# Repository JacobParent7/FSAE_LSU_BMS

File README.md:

# Motherboard

# Goal

Develop a distributed Battery Management System (BMS) for LSU FSAE's electric accumulator to be used in 2026 competition, targeting completion by May, 2025. All hardware and firmware development will be documented in this repository.

# Contact Info
### Motherboard Design
- Jacob Parent - jparen6@lsu.edu
### Daughterboard Design
- Parth Mistry - pmistr2@lsu.edu
- Modhy Alsahood - malsah1@lsu.edu

# FSAE BMS Design Log

## System Level Description 

## Orion BMS Thermistor Expansion Reverse Engineering

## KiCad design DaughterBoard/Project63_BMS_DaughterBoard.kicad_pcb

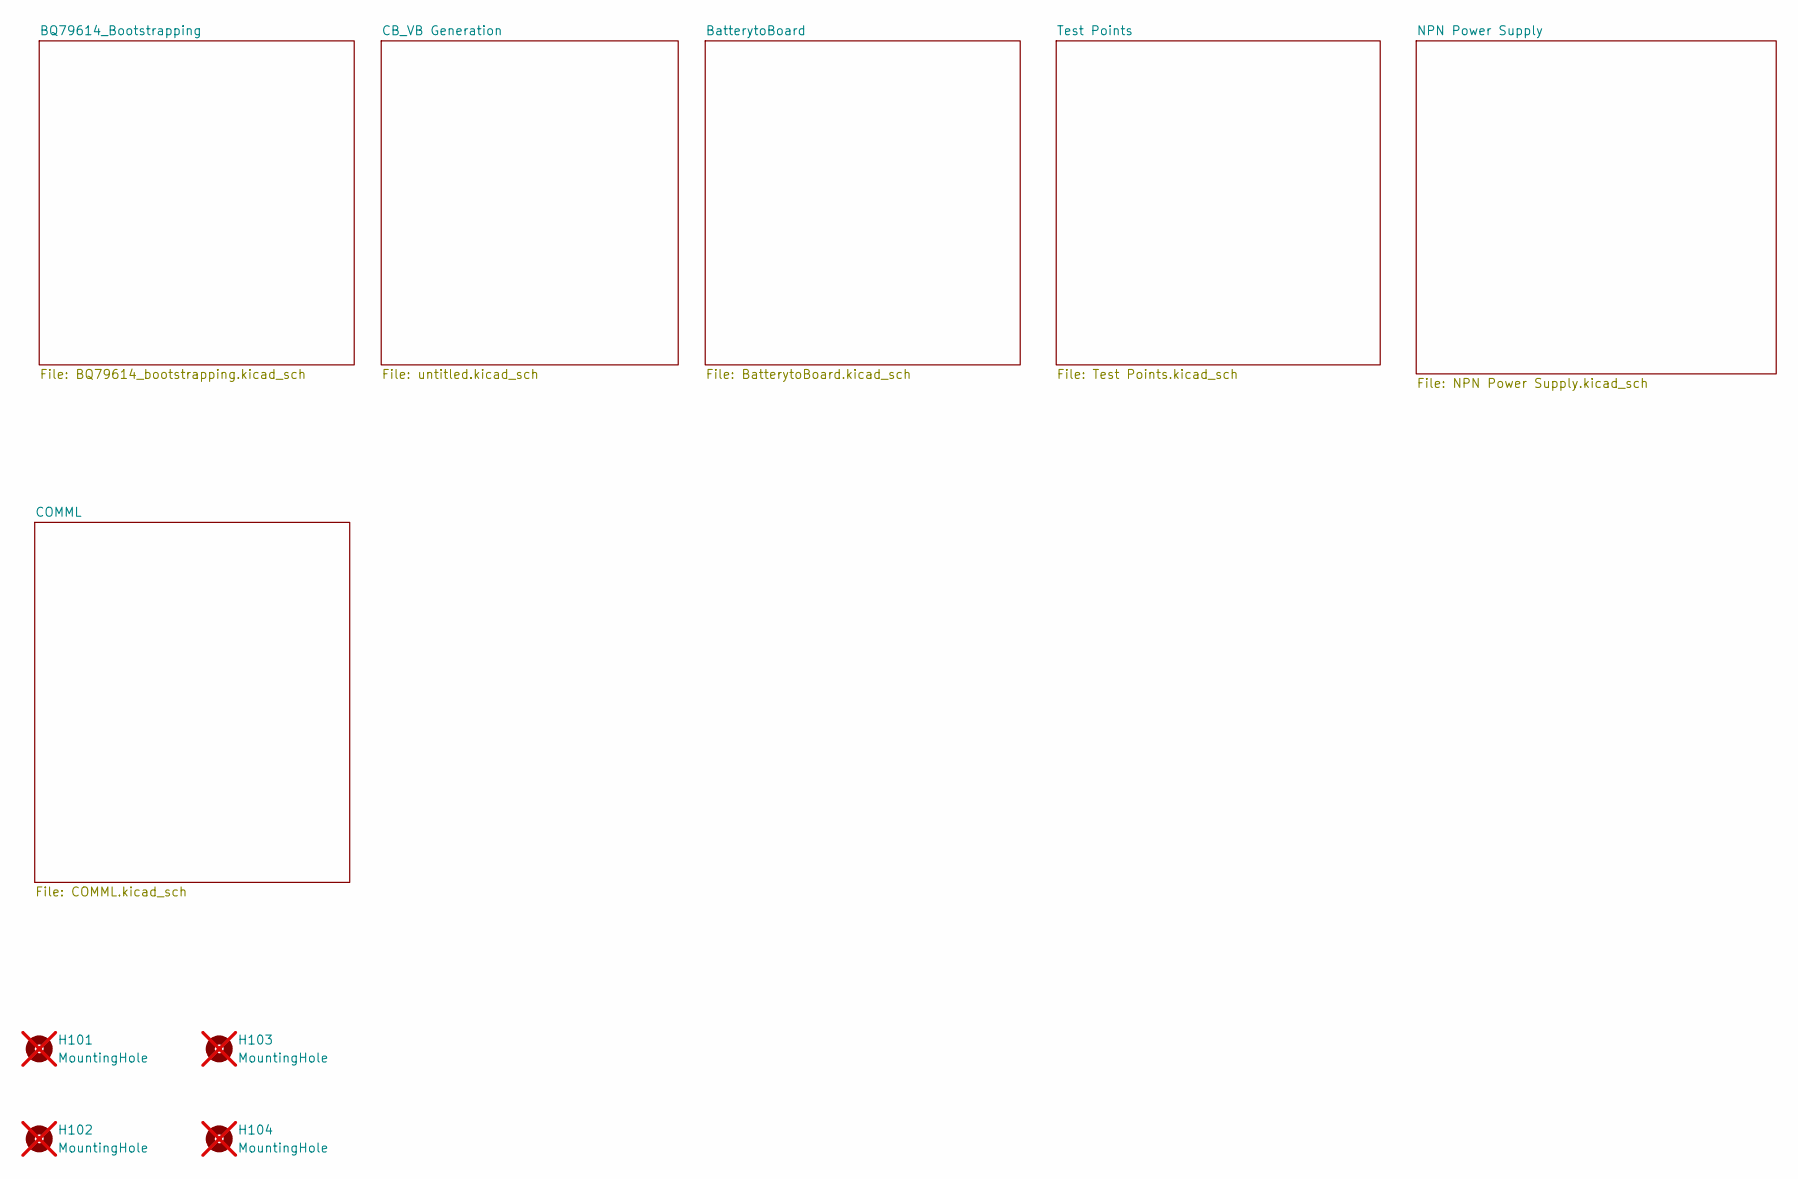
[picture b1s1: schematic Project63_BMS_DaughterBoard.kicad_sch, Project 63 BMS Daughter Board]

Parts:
H101, H102, H103, H104: MountingHole; MountingHole_3.2mm_M3; not fitted

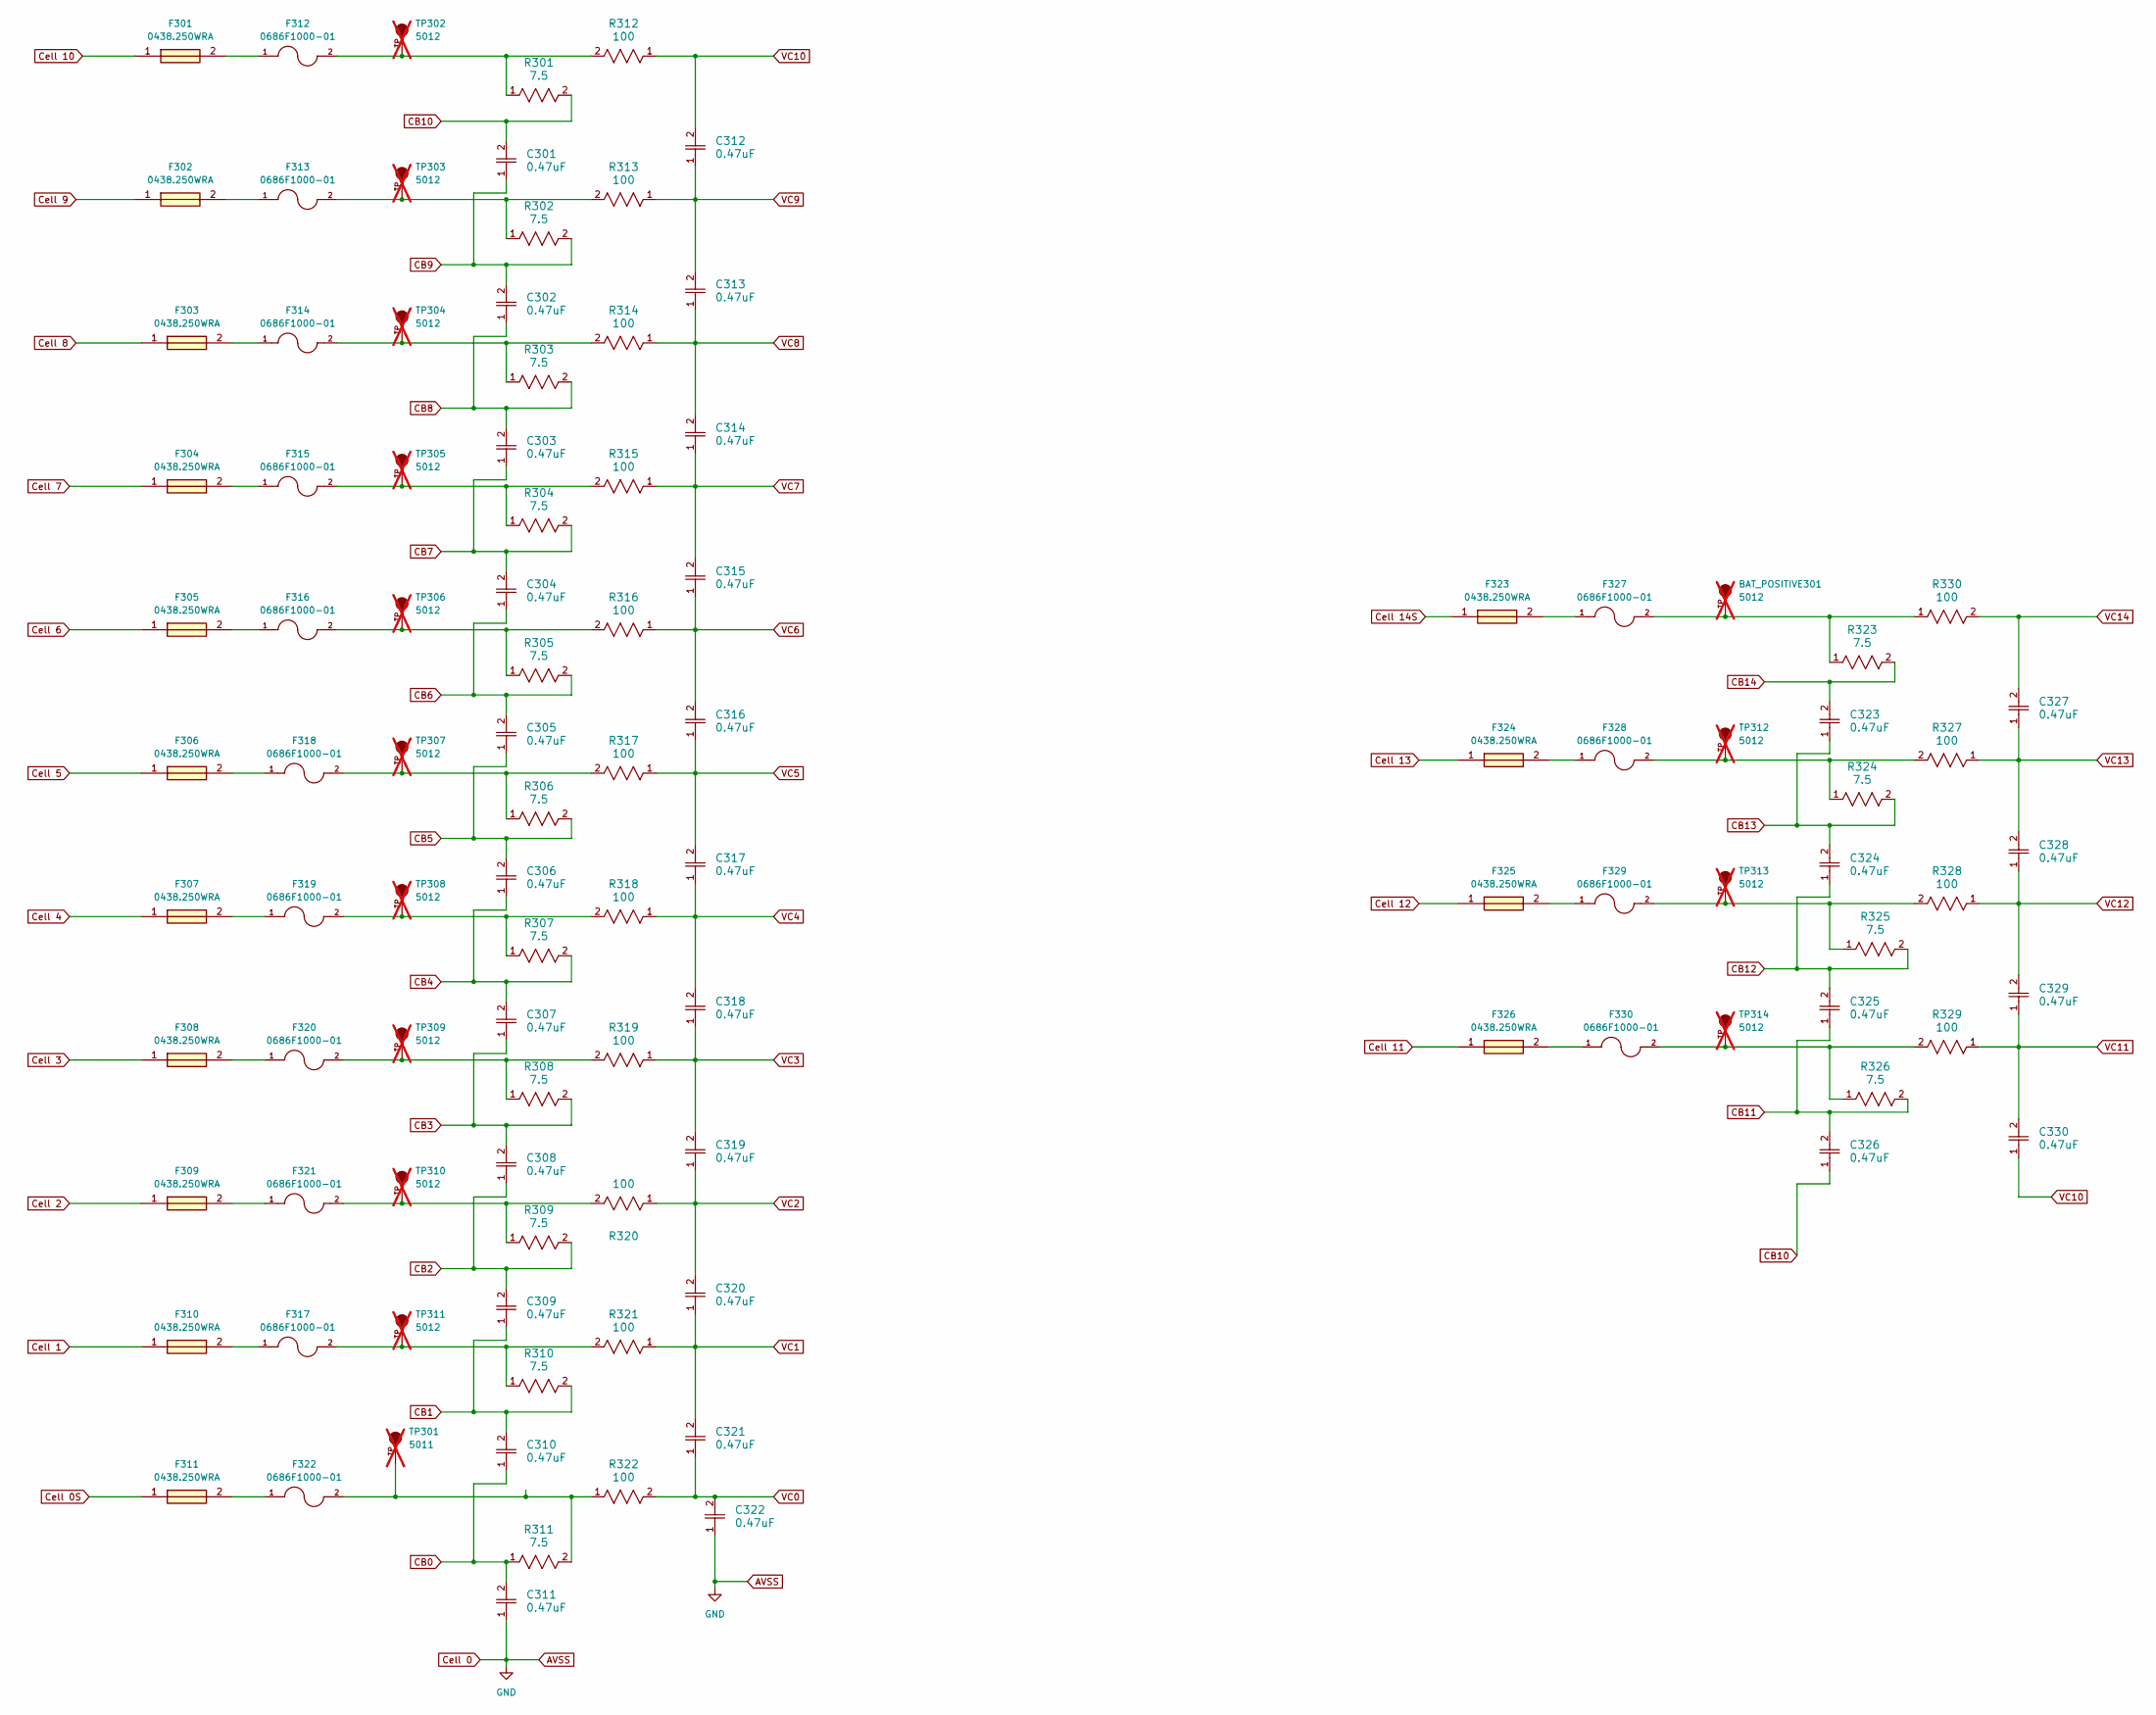
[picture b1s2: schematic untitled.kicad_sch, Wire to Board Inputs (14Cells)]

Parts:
BAT_POSITIVE301: 5012; TP_5012; PARTREV F; not fitted
C301, C302, C303, C304, C305, C306, C307, C308, C309, C310, C311, C312, C313, C314, C315, C316, C317, C318, C319, C320, C321, C322, C323, C324, C325, C326, C327, C328, C329, C330: 0.47uF; G-188_MUR-L; Manufacturer Part Number GCM188R71C474KA55D; JLC PCB Part # C161214
F301, F302, F303, F304, F305, F306, F307, F308, F309, F310, F311, F323, F324, F325, F326: 0438.250WRA; Fuse_0603_1608Metric; Manufacturer_Part_Number 0438.250WRA; Mouser Part Number 576-0438.250WRA
F312, F313, F314, F315, F316, F317, F318, F319, F320, F321, F322, F327, F328, F329, F330: 0686F1000-01; FUSC1608X60N; PARTREV Jan2019; JLC PCB Part # C136329
R301, R302, R303, R304, R305, R306, R307, R308, R309, R310, R311, R323, R324, R325, R326: 7.5; R_1812_4532Metric; Manufacturer Part Number FRC1812J7R5 TS; JLC PCB Part # C5204035
R312, R313, R314, R315, R316, R317, R318, R319, R320, R321, R322, R327, R328, R329, R330: 100; R_0603_1608Metric; Manufacturer Part Number HoAR0603-1/10W-100R-0.1%-TCR25; JLC PCB Part # C5123580
TP301: 5011; TP_5011; PARTREV F; not fitted
TP302, TP303, TP304, TP305, TP306, TP307, TP308, TP309, TP310, TP311, TP312, TP313, TP314: 5012; TP_5012; PARTREV F; not fitted

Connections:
AVSS: C311.1, C322.1; also elsewhere on the board
CB0: C310.1, C311.2, R311.1; also elsewhere on the board
CB1: C309.1, C310.2, R310.2; also elsewhere on the board
CB2: C308.1, C309.2, R309.2; also elsewhere on the board
CB3: C307.1, C308.2, R308.2; also elsewhere on the board
CB4: C306.1, C307.2, R307.2; also elsewhere on the board
CB5: C305.1, C306.2, R306.2; also elsewhere on the board
CB6: C304.1, C305.2, R305.2; also elsewhere on the board
CB7: C303.1, C304.2, R304.2; also elsewhere on the board
CB8: C302.1, C303.2, R303.2; also elsewhere on the board
CB9: C301.1, C302.2, R302.2; also elsewhere on the board
CB10: C301.2, C326.1, R301.2; also elsewhere on the board
CB11: C325.1, C326.2, R326.2; also elsewhere on the board
CB12: C324.1, C325.2, R325.2; also elsewhere on the board
CB13: C323.1, C324.2, R324.2; also elsewhere on the board
CB14: C323.2, R323.2; also elsewhere on the board
Cell 0S: F311.1; also elsewhere on the board
Cell 1: F310.1; also elsewhere on the board
Cell 2: F309.1; also elsewhere on the board
Cell 3: F308.1; also elsewhere on the board
Cell 4: F307.1; also elsewhere on the board
Cell 5: F306.1; also elsewhere on the board
Cell 6: F305.1; also elsewhere on the board
Cell 7: F304.1; also elsewhere on the board
Cell 8: F303.1; also elsewhere on the board
Cell 9: F302.1; also elsewhere on the board
Cell 10: F301.1; also elsewhere on the board
Cell 11: F326.1; also elsewhere on the board
Cell 12: F325.1; also elsewhere on the board
Cell 13: F324.1; also elsewhere on the board
Cell 14S: F323.1; also elsewhere on the board
unnamed: BAT_POSITIVE301.TP, F327.2, R323.1, R330.1
unnamed: F301.2, F312.1
unnamed: F302.2, F313.1
unnamed: F303.2, F314.1
unnamed: F304.2, F315.1
unnamed: F305.2, F316.1
unnamed: F306.2, F318.1
unnamed: F307.2, F319.1
unnamed: F308.2, F320.1
unnamed: F309.2, F321.1
unnamed: F310.2, F317.1
unnamed: F311.2, F322.1
unnamed: F312.2, R301.1, R312.2, TP302.TP
unnamed: F313.2, R302.1, R313.2, TP303.TP
unnamed: F314.2, R303.1, R314.2, TP304.TP
unnamed: F315.2, R304.1, R315.2, TP305.TP
unnamed: F316.2, R305.1, R316.2, TP306.TP
unnamed: F317.2, R310.1, R321.2, TP311.TP
unnamed: F318.2, R306.1, R317.2, TP307.TP
unnamed: F319.2, R307.1, R318.2, TP308.TP
unnamed: F320.2, R308.1, R319.2, TP309.TP
unnamed: F321.2, R309.1, R320.2, TP310.TP
unnamed: F322.2, R311.2, R322.1, TP301.TP
unnamed: F323.2, F327.1
unnamed: F324.2, F328.1
unnamed: F325.2, F329.1
unnamed: F326.2, F330.1
unnamed: F328.2, R324.1, R327.2, TP312.TP
unnamed: F329.2, R325.1, R328.2, TP313.TP
unnamed: F330.2, R326.1, R329.2, TP314.TP
VC0: C321.1, C322.2, R322.2; also elsewhere on the board
VC1: C320.1, C321.2, R321.1; also elsewhere on the board
VC2: C319.1, C320.2, R320.1; also elsewhere on the board
VC3: C318.1, C319.2, R319.1; also elsewhere on the board
VC4: C317.1, C318.2, R318.1; also elsewhere on the board
VC5: C316.1, C317.2, R317.1; also elsewhere on the board
VC6: C315.1, C316.2, R316.1; also elsewhere on the board
VC7: C314.1, C315.2, R315.1; also elsewhere on the board
VC8: C313.1, C314.2, R314.1; also elsewhere on the board
VC9: C312.1, C313.2, R313.1; also elsewhere on the board
VC10: C312.2, C330.1, R312.1; also elsewhere on the board
VC11: C329.1, C330.2, R329.1; also elsewhere on the board
VC12: C328.1, C329.2, R328.1; also elsewhere on the board
VC13: C327.1, C328.2, R327.1; also elsewhere on the board
VC14: C327.2, R330.2; also elsewhere on the board

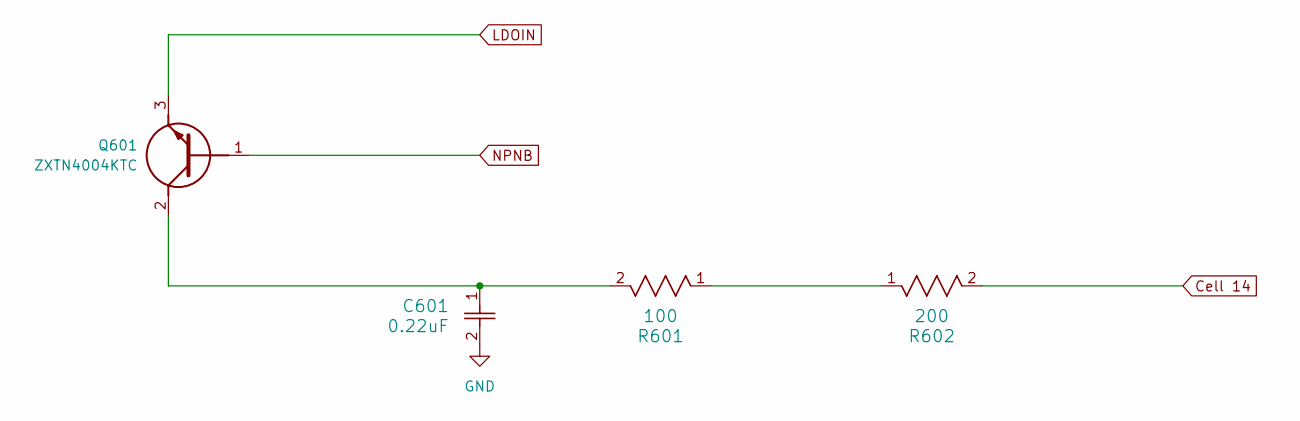
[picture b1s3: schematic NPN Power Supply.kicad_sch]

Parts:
C601: 0.22uF; G-31_MUR-L; Manufacturer Part Number GCM31MR72A224KA37L; JLC PCB Part # C161277
Q601: ZXTN4004KTC; Mouser Part Number 621-ZXTN4004KTC
R601: 100; RES_CRCW_2010-L; Manufacturer Part Number WF20P1000FTL; JLC PCB Part # C305269
R602: 200; R_2512_6332Metric; Manufacturer Part Number RC2512JK-07200RL; JLC PCB Part # C2935248

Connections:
AVSS: C601.2; also elsewhere on the board
BAT: R602.2; also elsewhere on the board
LDOIN: Q601.3 (E); also elsewhere on the board
NPNB: Q601.1 (B); also elsewhere on the board
unnamed: C601.1, Q601.2 (C), R601.2
unnamed: R601.1, R602.1

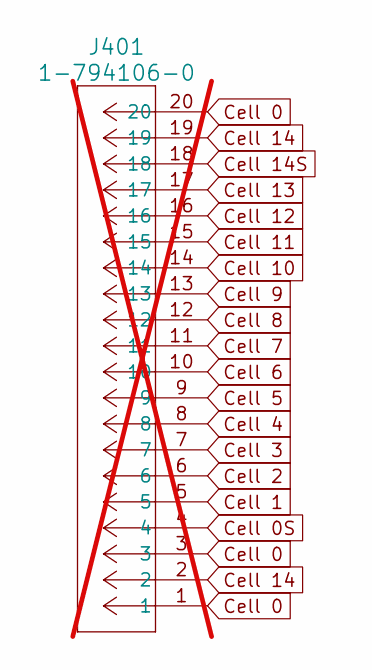
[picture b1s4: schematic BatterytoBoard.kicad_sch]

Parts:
J401: 1-794106-0; CON20_2X10_P4.14MM_RAMNL_TYC; not fitted

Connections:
AVSS: J401.1, J401.3, J401.20; also elsewhere on the board
BAT: J401.2, J401.19; also elsewhere on the board
Cell 0S: J401.4; also elsewhere on the board
Cell 1: J401.5; also elsewhere on the board
Cell 2: J401.6; also elsewhere on the board
Cell 3: J401.7; also elsewhere on the board
Cell 4: J401.8; also elsewhere on the board
Cell 5: J401.9; also elsewhere on the board
Cell 6: J401.10; also elsewhere on the board
Cell 7: J401.11; also elsewhere on the board
Cell 8: J401.12; also elsewhere on the board
Cell 9: J401.13; also elsewhere on the board
Cell 10: J401.14; also elsewhere on the board
Cell 11: J401.15; also elsewhere on the board
Cell 12: J401.16; also elsewhere on the board
Cell 13: J401.17; also elsewhere on the board
Cell 14S: J401.18; also elsewhere on the board

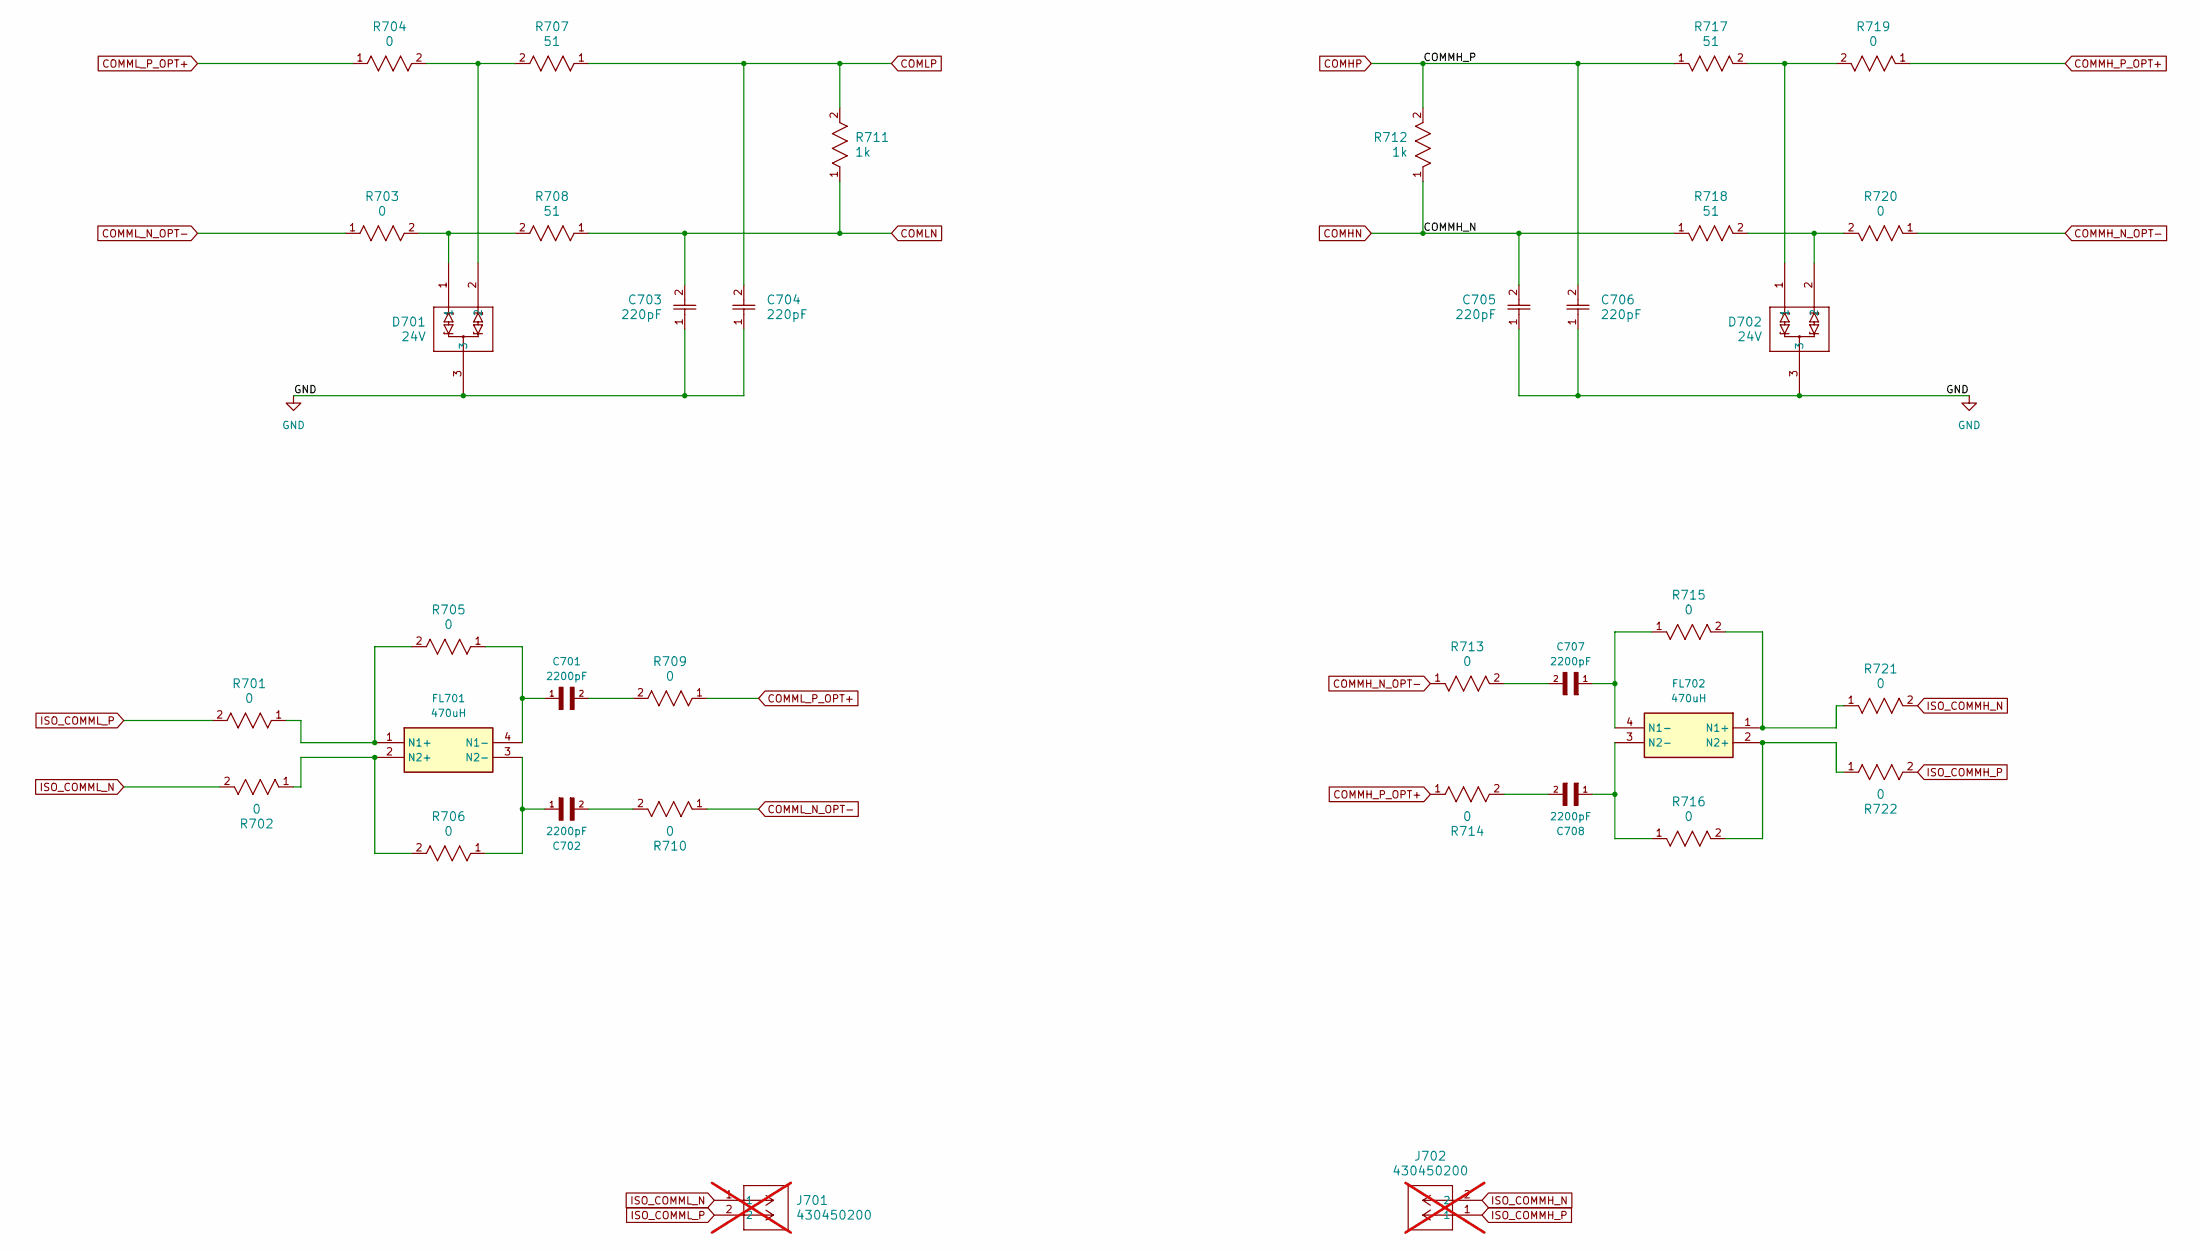
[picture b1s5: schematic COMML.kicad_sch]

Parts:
C701, C702, C707, C708: 2200pF; CAPC3216X160N; Manufacturer Part Number CC1206KKX7RCBB222; JLC PCB Part # C107194
C703, C704, C705, C706: 220pF; CAP_CL10_SAM-L; Manufacturer Part Number CC0603KRX7R9BB221; JLC PCB Part # C107081
D701, D702: 24V; SOT-23; Manufacturer Part Number PESD24VL2BTN; JLC PCB Part # C314266
FL701, FL702: 470uH; 744242471; Mouser Part Number 710-744242471
J701, J702: 430450200; CON_430450200_MOL; not fitted
R701, R702, R705, R706, R709, R710, R713, R714, R715, R716, R721, R722: 0; RES_CRCW_0805_VIS-L; Manufacturer Part Number CRCW08050000Z0EAHP; JLC PCB Part # C844811
R703, R704, R719, R720: 0; RC0603N_YAG-L; Manufacturer Part Number RC0603JR-070RL; JLC PCB Part # C95177
R707, R708, R717, R718: 51; RC0603N_VIS-L; Manufacturer Part Number CRCW060351R0JNEA; JLC PCB Part # C844178
R711, R712: 1k; RC0603N_PAN-L; Manufacturer Part Number FRC0603F1001TS; JLC PCB Part # C2907002

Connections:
AVSS: C703.1, C704.1, C705.1, C706.1, D701.3, D702.3; also elsewhere on the board
COMHN: C705.2, R712.1, R718.1; also elsewhere on the board
COMHP: C706.2, R712.2, R717.1; also elsewhere on the board
COMLN: C703.2, R708.1, R711.1; also elsewhere on the board
COMLP: C704.2, R707.1, R711.2; also elsewhere on the board
COMMH_N_OPT-: R713.1, R720.1
COMMH_P_OPT+: R714.1, R719.1
COMML_N_OPT-: R703.1, R710.1
COMML_P_OPT+: R704.1, R709.1
ISO_COMMH_N: J702.2, R721.2
ISO_COMMH_P: J702.1, R722.2
ISO_COMML_N: J701.1, R702.2
ISO_COMML_P: J701.2, R701.2
unnamed: C701.2, R709.2
unnamed: C702.2, R710.2
unnamed: C707.2, R713.2
unnamed: C708.2, R714.2
unnamed: D701.1, R703.2, R708.2
unnamed: D701.2, R704.2, R707.2
unnamed: D702.1, R717.2, R719.2
unnamed: D702.2, R718.2, R720.2
unnamed: FL701.1 (N1+), R701.1, R705.2
unnamed: C701.1, FL701.4 (N1-), R705.1
unnamed: FL701.2 (N2+), R702.1, R706.2
unnamed: C702.1, FL701.3 (N2-), R706.1
unnamed: FL702.1 (N1+), R715.2, R721.1
unnamed: C707.1, FL702.4 (N1-), R715.1
unnamed: FL702.2 (N2+), R716.2, R722.1
unnamed: C708.1, FL702.3 (N2-), R716.1

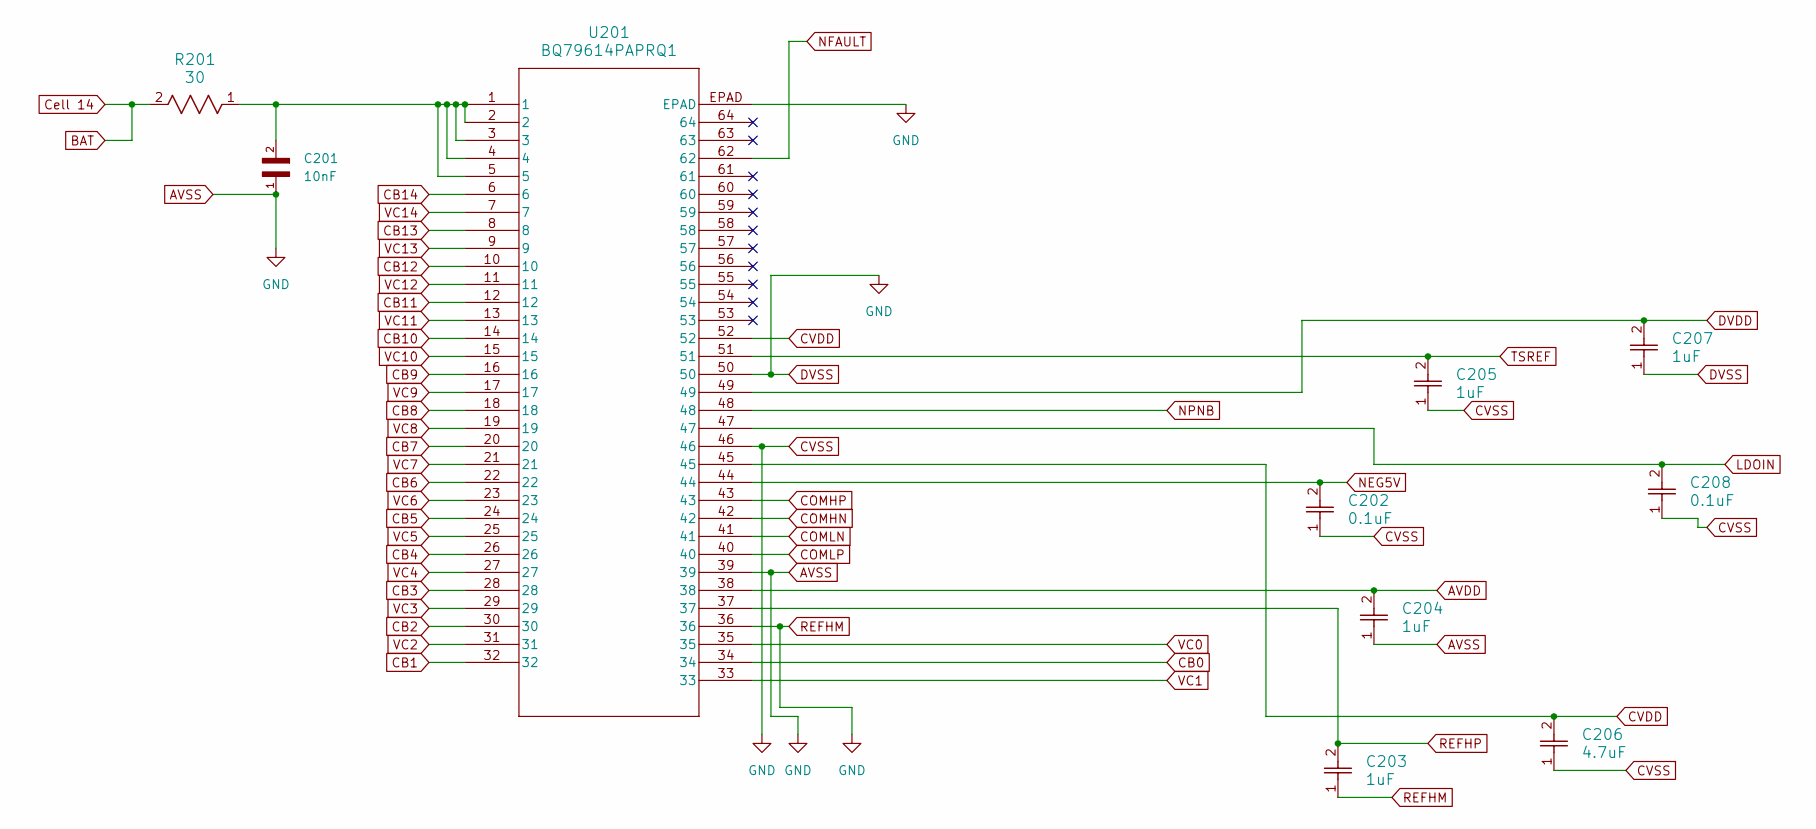
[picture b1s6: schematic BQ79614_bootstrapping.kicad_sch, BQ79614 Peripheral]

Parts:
C201: 10nF; CAPC1608X90N; Manufacturer Part Number GCM188R72A103KA37J; JLC PCB Part # C2167085
C202, C208: 0.1uF; CAP_GCM15_1p05X0p55X0p55_MUR-L; Manufacturer Part Number GCM155R71A104KA55D; JLC PCB Part # C161163
C203, C204, C205, C207: 1uF; CAPC18095_95N_KEM-L; Manufacturer Part Number CL10B105KA8NNNC; JLC PCB Part # C29936
C206: 4.7uF; CAP_2012_TDK-L; Manufacturer Part Number CC0805KKX7R7BB475; JLC PCB Part # C277499
R201: 30; RC0603N_PAN-L; Manufacturer Part Number ERJ-3EKF30R0V; JLC PCB Part # C403150
U201: BQ79614PAPRQ1; QFP_4PAPRQ1_TEX-L; Manufacturer Part Number BQ79616PAPRQ1; JLC PCB Part # C3682338

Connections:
AVDD: C204.2, U201.38; also elsewhere on the board
AVSS: C201.1, C202.1, C203.1, C204.1, C205.1, C206.1, C207.1, C208.1, U201.36, U201.39, U201.46, U201.50, U201.EPAD; also elsewhere on the board
BAT: R201.2; also elsewhere on the board
CB0: U201.34; also elsewhere on the board
CB1: U201.32; also elsewhere on the board
CB2: U201.30; also elsewhere on the board
CB3: U201.28; also elsewhere on the board
CB4: U201.26; also elsewhere on the board
CB5: U201.24; also elsewhere on the board
CB6: U201.22; also elsewhere on the board
CB7: U201.20; also elsewhere on the board
CB8: U201.18; also elsewhere on the board
CB9: U201.16; also elsewhere on the board
CB10: U201.14; also elsewhere on the board
CB11: U201.12; also elsewhere on the board
CB12: U201.10; also elsewhere on the board
CB13: U201.8; also elsewhere on the board
CB14: U201.6; also elsewhere on the board
COMHN: U201.42; also elsewhere on the board
COMHP: U201.43; also elsewhere on the board
COMLN: U201.41; also elsewhere on the board
COMLP: U201.40; also elsewhere on the board
CVDD: C206.2, U201.45, U201.52; also elsewhere on the board
DVDD: C207.2, U201.49; also elsewhere on the board
LDOIN: C208.2, U201.47; also elsewhere on the board
NEG5V: C202.2, U201.44; also elsewhere on the board
NFAULT: U201.62; also elsewhere on the board
NPNB: U201.48; also elsewhere on the board
unnamed: C201.2, R201.1, U201.1, U201.2, U201.3, U201.4, U201.5
REFHP: C203.2, U201.37; also elsewhere on the board
TSREF: C205.2, U201.51; also elsewhere on the board
VC0: U201.35; also elsewhere on the board
VC1: U201.33; also elsewhere on the board
VC2: U201.31; also elsewhere on the board
VC3: U201.29; also elsewhere on the board
VC4: U201.27; also elsewhere on the board
VC5: U201.25; also elsewhere on the board
VC6: U201.23; also elsewhere on the board
VC7: U201.21; also elsewhere on the board
VC8: U201.19; also elsewhere on the board
VC9: U201.17; also elsewhere on the board
VC10: U201.15; also elsewhere on the board
VC11: U201.13; also elsewhere on the board
VC12: U201.11; also elsewhere on the board
VC13: U201.9; also elsewhere on the board
VC14: U201.7; also elsewhere on the board

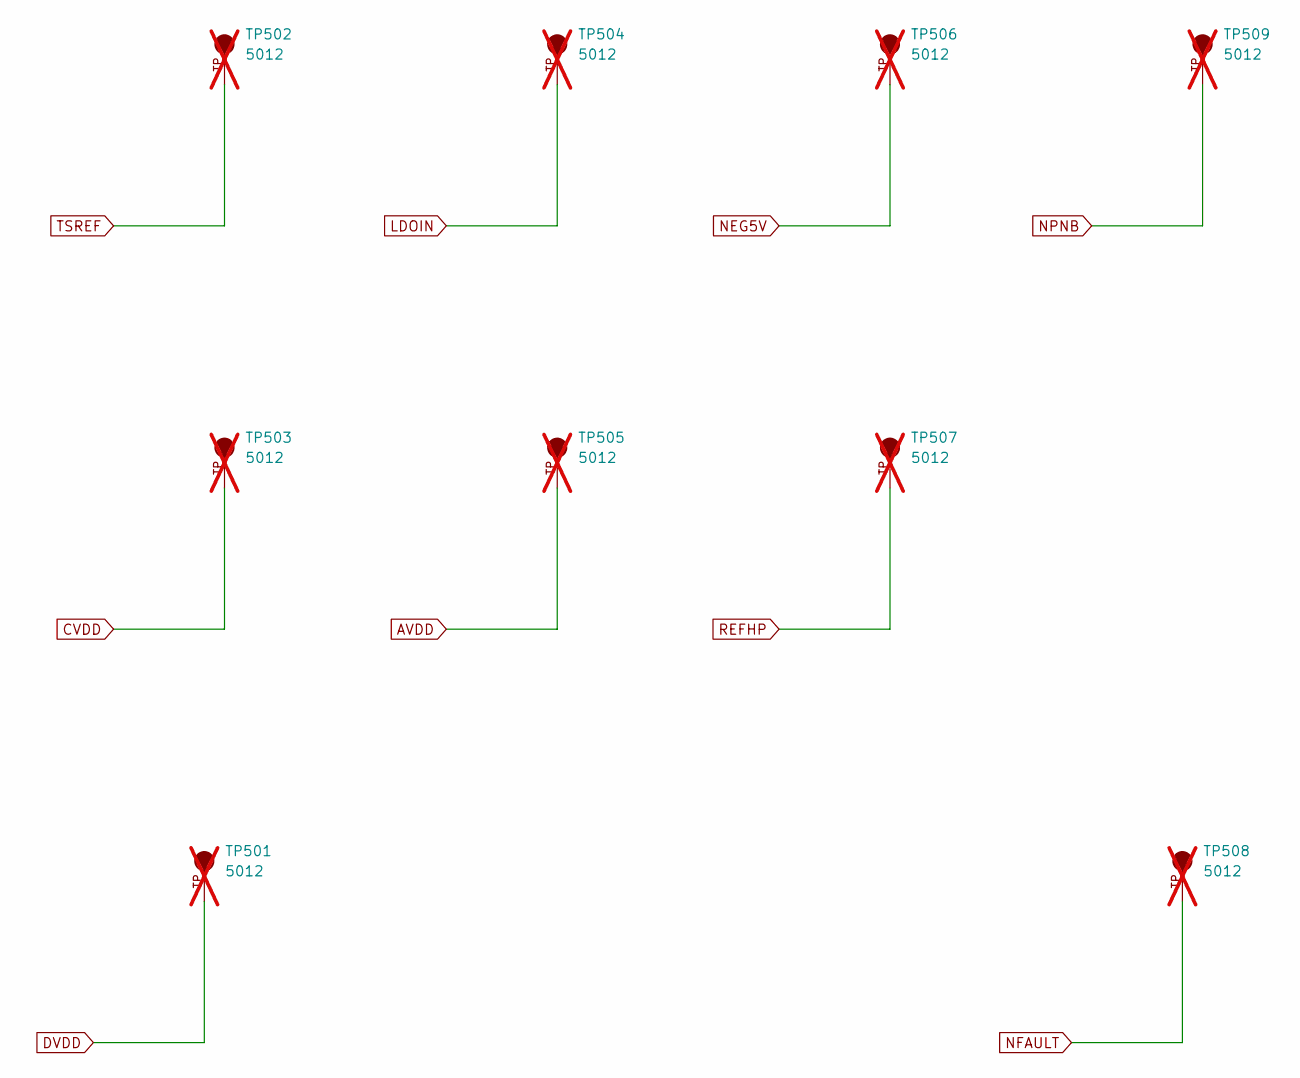
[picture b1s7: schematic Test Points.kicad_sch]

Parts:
TP501, TP502, TP503, TP504, TP505, TP506, TP507, TP508, TP509: 5012; TP_5012; PARTREV F; not fitted

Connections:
AVDD: TP505.TP; also elsewhere on the board
CVDD: TP503.TP; also elsewhere on the board
DVDD: TP501.TP; also elsewhere on the board
LDOIN: TP504.TP; also elsewhere on the board
NEG5V: TP506.TP; also elsewhere on the board
NFAULT: TP508.TP; also elsewhere on the board
NPNB: TP509.TP; also elsewhere on the board
REFHP: TP507.TP; also elsewhere on the board
TSREF: TP502.TP; also elsewhere on the board
